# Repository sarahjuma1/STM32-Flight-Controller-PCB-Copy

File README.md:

# STM32-Based Flight Controller PCB

## Project Overview
Designed a 4-layer flight controller PCB around the STM32F405 microcontroller using KiCad. The project integrates motion sensing, environmental sensing, onboard memory, and communication interfaces for an embedded flight control system.

## Key Features
- STM32F405 ARM Cortex-M4 microcontroller
- ICM-42688-P 6-axis inertial measurement unit
- BMP390 barometric pressure sensor
- SPI flash memory
- USB-C and SWD interfaces
- Four ESC PWM output connections
- Power regulation, reverse-polarity protection, and filtering

## Tools & Technologies
KiCad, STM32, I²C, SPI, USB-C, PCB Design, Embedded Systems

## Design Process
1. Designed the circuit schematic and integrated components.
2. Implemented communication and power interfaces.
3. Performed electrical rule checking (ERC).
4. Assigned footprints and developed a 4-layer PCB layout.

## Project Status
Personal PCB design project. Hardware manufacturing and physical testing have not been completed.

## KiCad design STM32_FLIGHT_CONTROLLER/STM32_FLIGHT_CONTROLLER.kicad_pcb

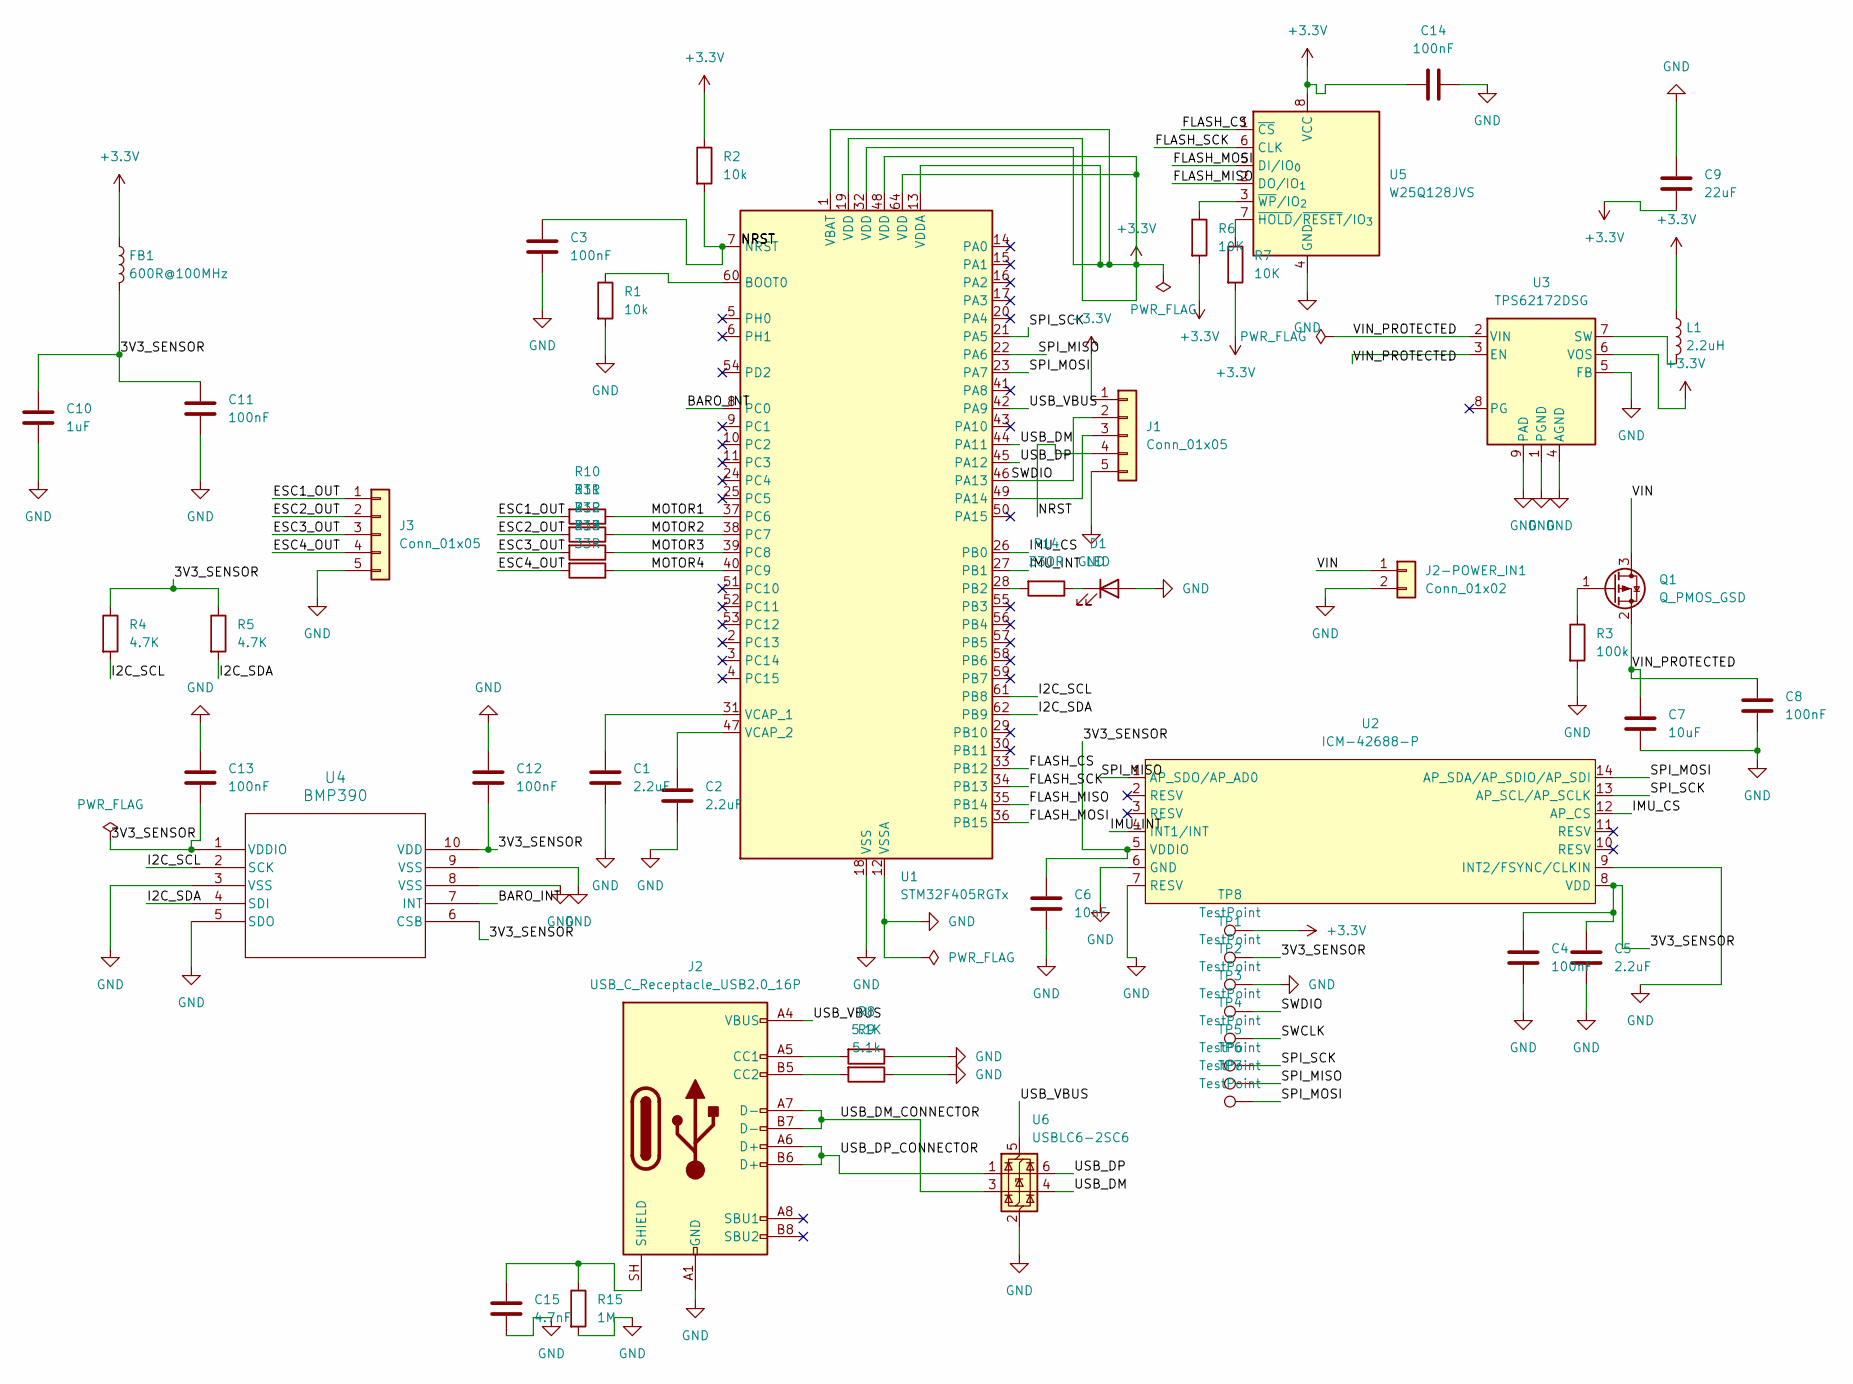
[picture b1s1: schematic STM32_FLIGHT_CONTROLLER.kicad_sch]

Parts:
C1, C2, C5: 2.2uF; C_0603_1608Metric
C3, C4, C8, C11, C12, C13, C14: 100nF; C_0603_1608Metric
C6: 10nF; C_0603_1608Metric
C7: 10uF; C_1206_3216Metric
C9: 22uF; C_1206_3216Metric
C10: 1uF; C_0603_1608Metric
C15: 4.7nF; C_0603_1608Metric
D1: LED; LED_0603_1608Metric
FB1: 600R@100MHz; L_0603_1608Metric
J1, J3: Conn_01x05; PinHeader_1x05_P2.54mm_Vertical
J2: USB_C_Receptacle_USB2.0_16P; USB_C_Receptacle_GCT_USB4105-xx-A_16P_TopMnt_Horizontal
J2-POWER_IN1: Conn_01x02; PinHeader_1x02_P2.54mm_Vertical
L1: 2.2uH; L_Coilcraft_LPS3010
Q1: Q_PMOS_GSD; SOT-23
R1, R2: 10k; R_0603_1608Metric
R3: 100k; R_0603_1608Metric
R4, R5: 4.7K; R_0603_1608Metric
R6, R7: 10K; R_0603_1608Metric
R8: 5.1K; R_0603_1608Metric
R9: 5.1k; R_0603_1608Metric
R10, R11, R12, R13: 33R; R_0603_1608Metric
R14: 33OR; R_0603_1608Metric
R15: 1M; R_0603_1608Metric
TP1, TP2, TP3, TP4, TP5, TP6, TP7, TP8: TestPoint; TestPoint_Pad_D1.0mm
U1: STM32F405RGTx; LQFP-64_10x10mm_P0.5mm
U2: ICM-42688-P; LGA-14_L3.0-W2.5-P0.50-TL; MPN ICM-42688-P; LCSC Part C1850418
U3: TPS62172DSG; WSON-8-1EP_2x2mm_P0.5mm_EP0.9x1.6mm_ThermalVias
U4: BMP390
U5: W25Q128JVS; SOIC-8_5.3x5.3mm_P1.27mm
U6: USBLC6-2SC6; SOT-23-6

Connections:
+3.3V: C9.2, C14.2, FB1.1, J1.1, L1.1, R2.1, R6.2, R7.2, TP8.1 (1_1), U1.1 (VBAT), U1.13 (VDDA), U1.19 (VDD), U1.32 (VDD), U1.48 (VDD), U1.64 (VDD), U3.6 (VOS), U5.8 (VCC)
/3V3_SENSOR: C4.1, C5.1, C6.1, C10.1, C11.1, C12.2, C13.2, FB1.2, R4.1, R5.1, TP1.1 (1_1), U2.5 (VDDIO), U2.8 (VDD), U4.1 (VDDIO), U4.6 (CSB), U4.10 (VDD)
/BARO_INT: U1.8 (PC0), U4.7 (INT)
/ESC1_OUT: J3.1, R10.2
/ESC2_OUT: J3.2, R11.2
/ESC3_OUT: J3.3, R12.2
/ESC4_OUT: J3.4, R13.2
/FLASH_CS: U1.33 (PB12), U5.1 (~CS)
/FLASH_MISO: U1.35 (PB14), U5.2 (DO/IO_{1})
/FLASH_MOSI: U1.36 (PB15), U5.5 (DI/IO_{0})
/FLASH_SCK: U1.34 (PB13), U5.6 (CLK)
/I2C_SCL: R4.2, U1.61 (PB8), U4.2 (SCK)
/I2C_SDA: R5.2, U1.62 (PB9), U4.4 (SDI)
/IMU_CS: U1.26 (PB0), U2.12 (AP_CS)
/IMU_INT: U1.27 (PB1), U2.4 (INT1/INT)
/MOTOR1: R10.1, U1.37 (PC6)
/MOTOR2: R11.1, U1.38 (PC7)
/MOTOR3: R12.1, U1.39 (PC8)
/MOTOR4: R13.1, U1.40 (PC9)
/NRST: J1.4
/SPI_MISO: TP6.1 (1_1), U1.22 (PA6), U2.1 (AP_SDO/AP_AD0)
/SPI_MOSI: TP7.1 (1_1), U1.23 (PA7), U2.14 (AP_SDA/AP_SDIO/AP_SDI)
/SPI_SCK: TP5.1 (1_1), U1.21 (PA5), U2.13 (AP_SCL/AP_SCLK)
/SWCLK: TP4.1 (1_1)
/SWDIO: J1.2, TP3.1 (1_1), U1.46 (PA13)
/USB_DM: U1.44 (PA11), U6.4 (I/O2)
/USB_DM_CONNECTOR: J2.A7 (D-), J2.B7 (D-), U6.3 (I/O2)
/USB_DP: U1.45 (PA12), U6.6 (I/O1)
/USB_DP_CONNECTOR: J2.A6 (D+), J2.B6 (D+), U6.1 (I/O1)
/USB_VBUS: J2.A4 (VBUS), J2.A9 (VBUS), J2.B4 (VBUS), J2.B9 (VBUS), U1.42 (PA9), U6.5 (VBUS)
/VIN: J2-POWER_IN1.1, Q1.3 (D)
/VIN_PROTECTED: C7.1, C8.1, Q1.2 (S), U3.2 (VIN), U3.3 (EN)
GND: C1.2, C2.2, C3.2, C4.2, C5.2, C6.2, C7.2, C8.2, C9.1, C10.2, C11.2, C12.1, C13.1, C14.1, C15.2, D1.2 (A), J1.5, J2.A1 (GND), J2.A12 (GND), J2.B1 (GND), J2.B12 (GND), J2-POWER_IN1.2, J3.5, R1.2, R3.2, R8.1, R9.1, R15.2, TP2.1 (1_1), U1.12 (VSSA), U1.18 (VSS), U1.63 (VSS), U2.6 (GND), U2.7 (RESV), U2.9 (INT2/FSYNC/CLKIN), U3.1 (PGND), U3.4 (AGND), U3.5 (FB), U3.9 (PAD), U4.3 (VSS), U4.5 (SDO), U4.8 (VSS), U4.9 (VSS), U5.4 (GND), U6.2 (GND)
unnamed: D1.1 (K), R14.1
unnamed: J1.3, U1.49 (PA14)
unnamed: J2.A5 (CC1), R8.2
unnamed: J2.B5 (CC2), R9.2
unnamed: C15.1, J2.SH (SHIELD), R15.1
unnamed: Q1.1 (G), R3.1
unnamed: R1.1, U1.60 (BOOT0)
unnamed: C3.1, R2.2, U1.7 (NRST)
unnamed: R14.2, U1.28 (PB2)
unnamed: C1.1, U1.31 (VCAP_1)
unnamed: C2.1, U1.47 (VCAP_2)
unnamed: L1.2, U3.7 (SW)
unnamed: R7.1, U5.7 (~HOLD/~RESET/IO_{3})
unnamed: R6.1, U5.3 (~WP/IO_{2})

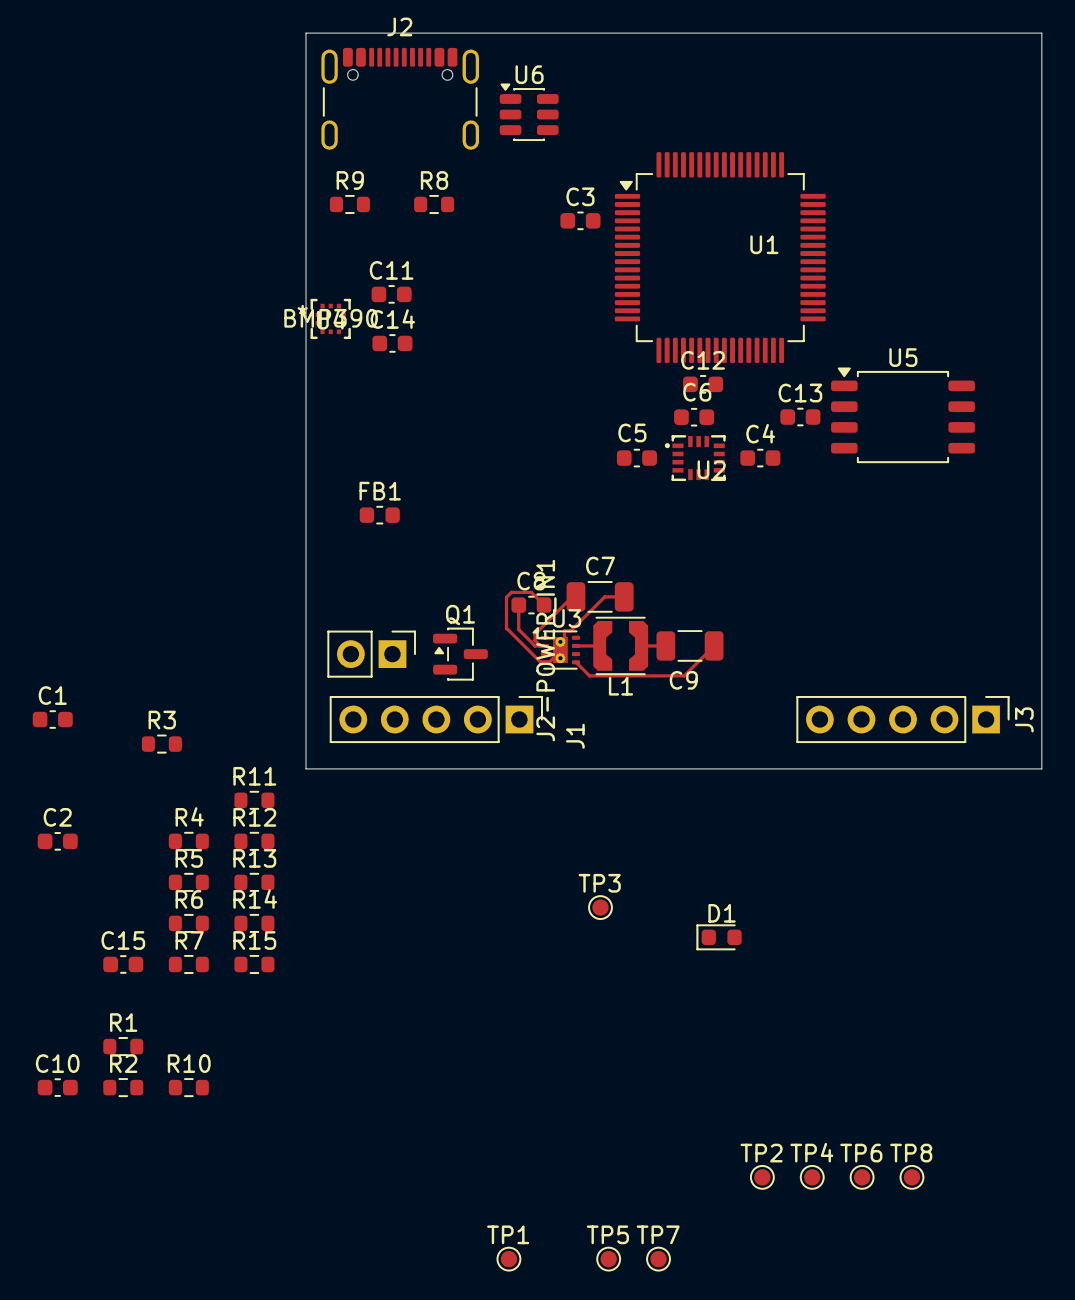
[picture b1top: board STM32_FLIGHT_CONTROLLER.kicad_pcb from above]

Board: 4 copper layers, 45.0 x 45.0 mm, 52 parts (0 on the bottom side), 45 nets.

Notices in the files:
parts and their libraries:
Copyright 2016 Accelerated Designs. All rights reserved.
